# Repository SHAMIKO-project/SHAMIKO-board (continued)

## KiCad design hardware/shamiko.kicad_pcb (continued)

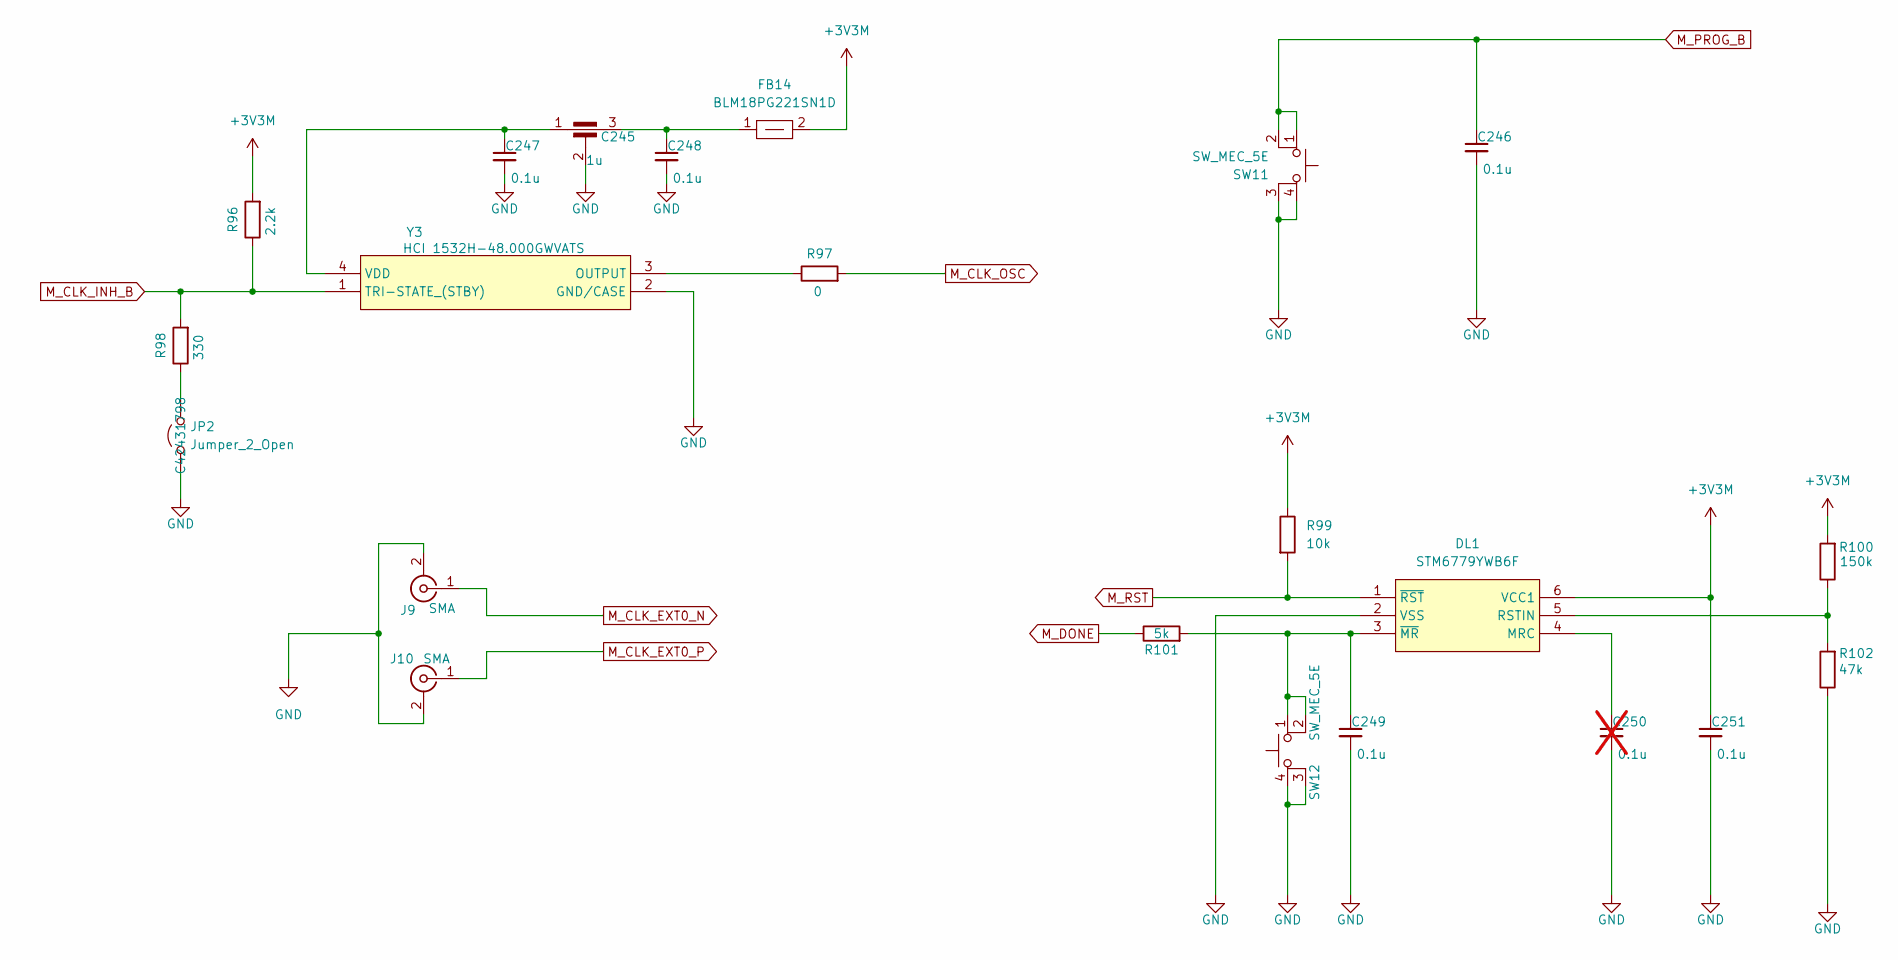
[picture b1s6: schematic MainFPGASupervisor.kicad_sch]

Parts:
C245: 1u; NFM31HK103R1H3L; LCSC C92518
C246, C247, C248, C249, C251: 0.1u; C_0603_1608Metric; LCSC C77055
C250: 0.1u; C_0603_1608Metric; LCSC C77055; not fitted
DL1: STM6779YWB6F; TSOT-23-6; LCSC C2802536
FB14: BLM18PG221SN1D; BLM18SP221SN1B; LCSC C80165
J9, J10: SMA; SMA_Amphenol_132134-14_Vertical; LCSC C3174425
JP2: Jumper_2_Open; PinHeader_1x02_P2.54mm_Vertical; LCSC C42431798
R96: 2.2k; R_0603_1608Metric; LCSC C114662
R97: 0; R_0603_1608Metric; LCSC C100044
R98: 330; R_0603_1608Metric; LCSC C105881
R99: 10k; R_0603_1608Metric; LCSC C95204
R100: 150k; R_0603_1608Metric; LCSC C2906993
R101: 5k; R_0603_1608Metric; LCSC C862232
R102: 47k; R_0603_1608Metric; LCSC C105579
SW11, SW12: SW_MEC_5E; MySW_PUSH_6mm_H5mm; LCSC C393938
Y3: HCI 1532H-48.000GWVATS; 1532H-48_000GWVATS; LCSC C51822787

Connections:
+3V3M: C251.1, DL1.6 (VCC1), FB14.2, R96.2, R99.1, R100.2; also elsewhere on the board
GND: C245.2, C246.2, C247.2, C248.2, C249.2, C250.2, C251.2, DL1.2 (VSS), J9.2 (Ext), J10.2 (Ext), JP2.1 (A), R102.1, SW11.3 (K), SW11.4 (A), SW12.3 (K), SW12.4 (A), Y3.2 (GND/CASE); also elsewhere on the board
M_CLK_EXT0_N: J9.1 (In); also elsewhere on the board
M_CLK_EXT0_P: J10.1 (In); also elsewhere on the board
M_CLK_INH_B: R96.1, R98.2, Y3.1 (TRI-STATE_(STBY)); also elsewhere on the board
M_CLK_OSC: R97.2; also elsewhere on the board
M_DONE: R101.1; also elsewhere on the board
M_PROG_B: C246.1, SW11.1, SW11.2; also elsewhere on the board
M_RST: DL1.1 (~RST), R99.2; also elsewhere on the board
unnamed: C245.3, C248.1, FB14.1
unnamed: C250.1, DL1.4 (MRC)
unnamed: DL1.5 (RSTIN), R100.1, R102.2
unnamed: C249.1, DL1.3 (~MR), R101.2, SW12.1, SW12.2
unnamed: JP2.2 (B), R98.1
unnamed: R97.1, Y3.3 (OUTPUT)
unnamed: C245.1, C247.1, Y3.4 (VDD)

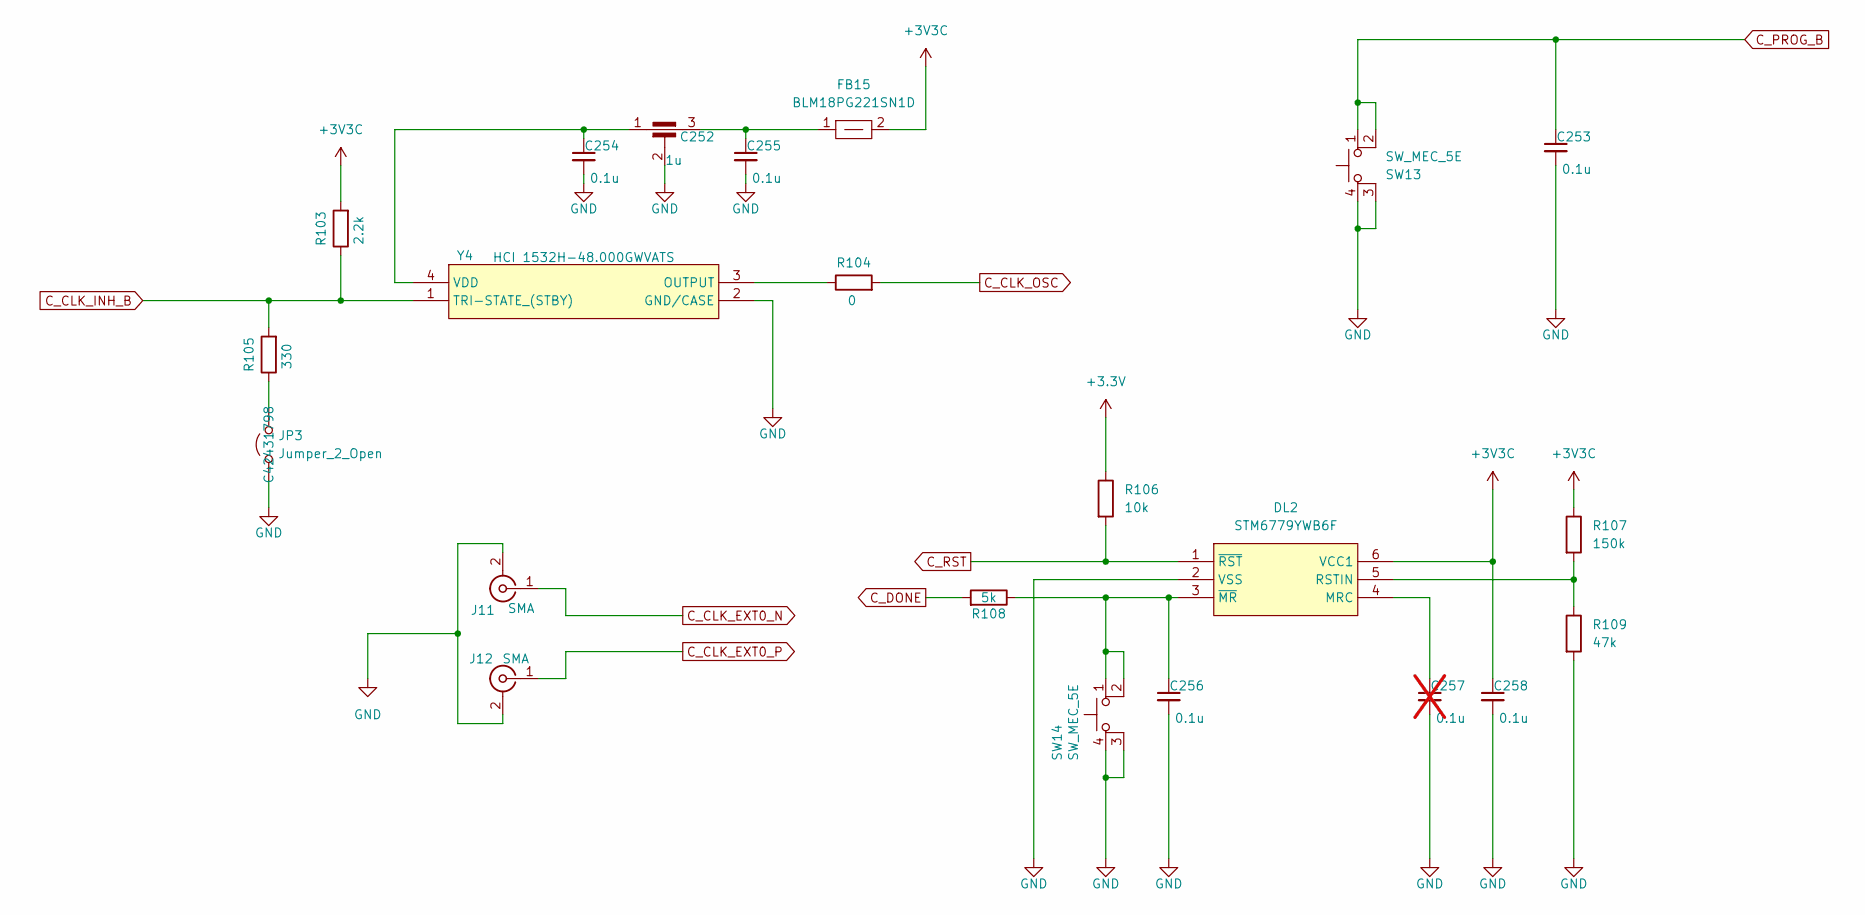
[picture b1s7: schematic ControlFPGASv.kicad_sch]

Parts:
C252: 1u; NFM31HK103R1H3L; LCSC C92518
C253, C254, C255, C256, C258: 0.1u; C_0603_1608Metric; LCSC C77055
C257: 0.1u; C_0603_1608Metric; LCSC C77055; not fitted
DL2: STM6779YWB6F; TSOT-23-6; LCSC C2802536
FB15: BLM18PG221SN1D; BLM18SP221SN1B; LCSC C80165
J11, J12: SMA; SMA_Amphenol_132134-14_Vertical; LCSC C3174425
JP3: Jumper_2_Open; PinHeader_1x02_P2.54mm_Vertical; LCSC C42431798
R103: 2.2k; R_0603_1608Metric; LCSC C114662
R104: 0; R_0603_1608Metric; LCSC C100044
R105: 330; R_0603_1608Metric; LCSC C105881
R106: 10k; R_0603_1608Metric; LCSC C95204
R107: 150k; R_0603_1608Metric; LCSC C2906993
R108: 5k; R_0603_1608Metric; LCSC C862232
R109: 47k; R_0603_1608Metric; LCSC C105579
SW13, SW14: SW_MEC_5E; MySW_PUSH_6mm_H5mm; LCSC C393938
Y4: HCI 1532H-48.000GWVATS; 1532H-48_000GWVATS; LCSC C51822787

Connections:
+3.3V: R106.1; also elsewhere on the board
+3V3C: C258.1, DL2.6 (VCC1), FB15.2, R103.2, R107.1; also elsewhere on the board
C_CLK_EXT0_N: J11.1 (In); also elsewhere on the board
C_CLK_EXT0_P: J12.1 (In); also elsewhere on the board
C_CLK_INH_B: R103.1, R105.2, Y4.1 (TRI-STATE_(STBY)); also elsewhere on the board
C_CLK_OSC: R104.2; also elsewhere on the board
C_DONE: R108.2; also elsewhere on the board
C_PROG_B: C253.1, SW13.1, SW13.2; also elsewhere on the board
C_RST: DL2.1 (~RST), R106.2; also elsewhere on the board
GND: C252.2, C253.2, C254.2, C255.2, C256.2, C257.2, C258.2, DL2.2 (VSS), J11.2 (Ext), J12.2 (Ext), JP3.1 (A), R109.2, SW13.3 (K), SW13.4 (A), SW14.3 (K), SW14.4 (A), Y4.2 (GND/CASE); also elsewhere on the board
unnamed: C252.3, C255.1, FB15.1
unnamed: C257.1, DL2.4 (MRC)
unnamed: DL2.5 (RSTIN), R107.2, R109.1
unnamed: C256.1, DL2.3 (~MR), R108.1, SW14.1, SW14.2
unnamed: JP3.2 (B), R105.1
unnamed: R104.1, Y4.3 (OUTPUT)
unnamed: C252.1, C254.1, Y4.4 (VDD)

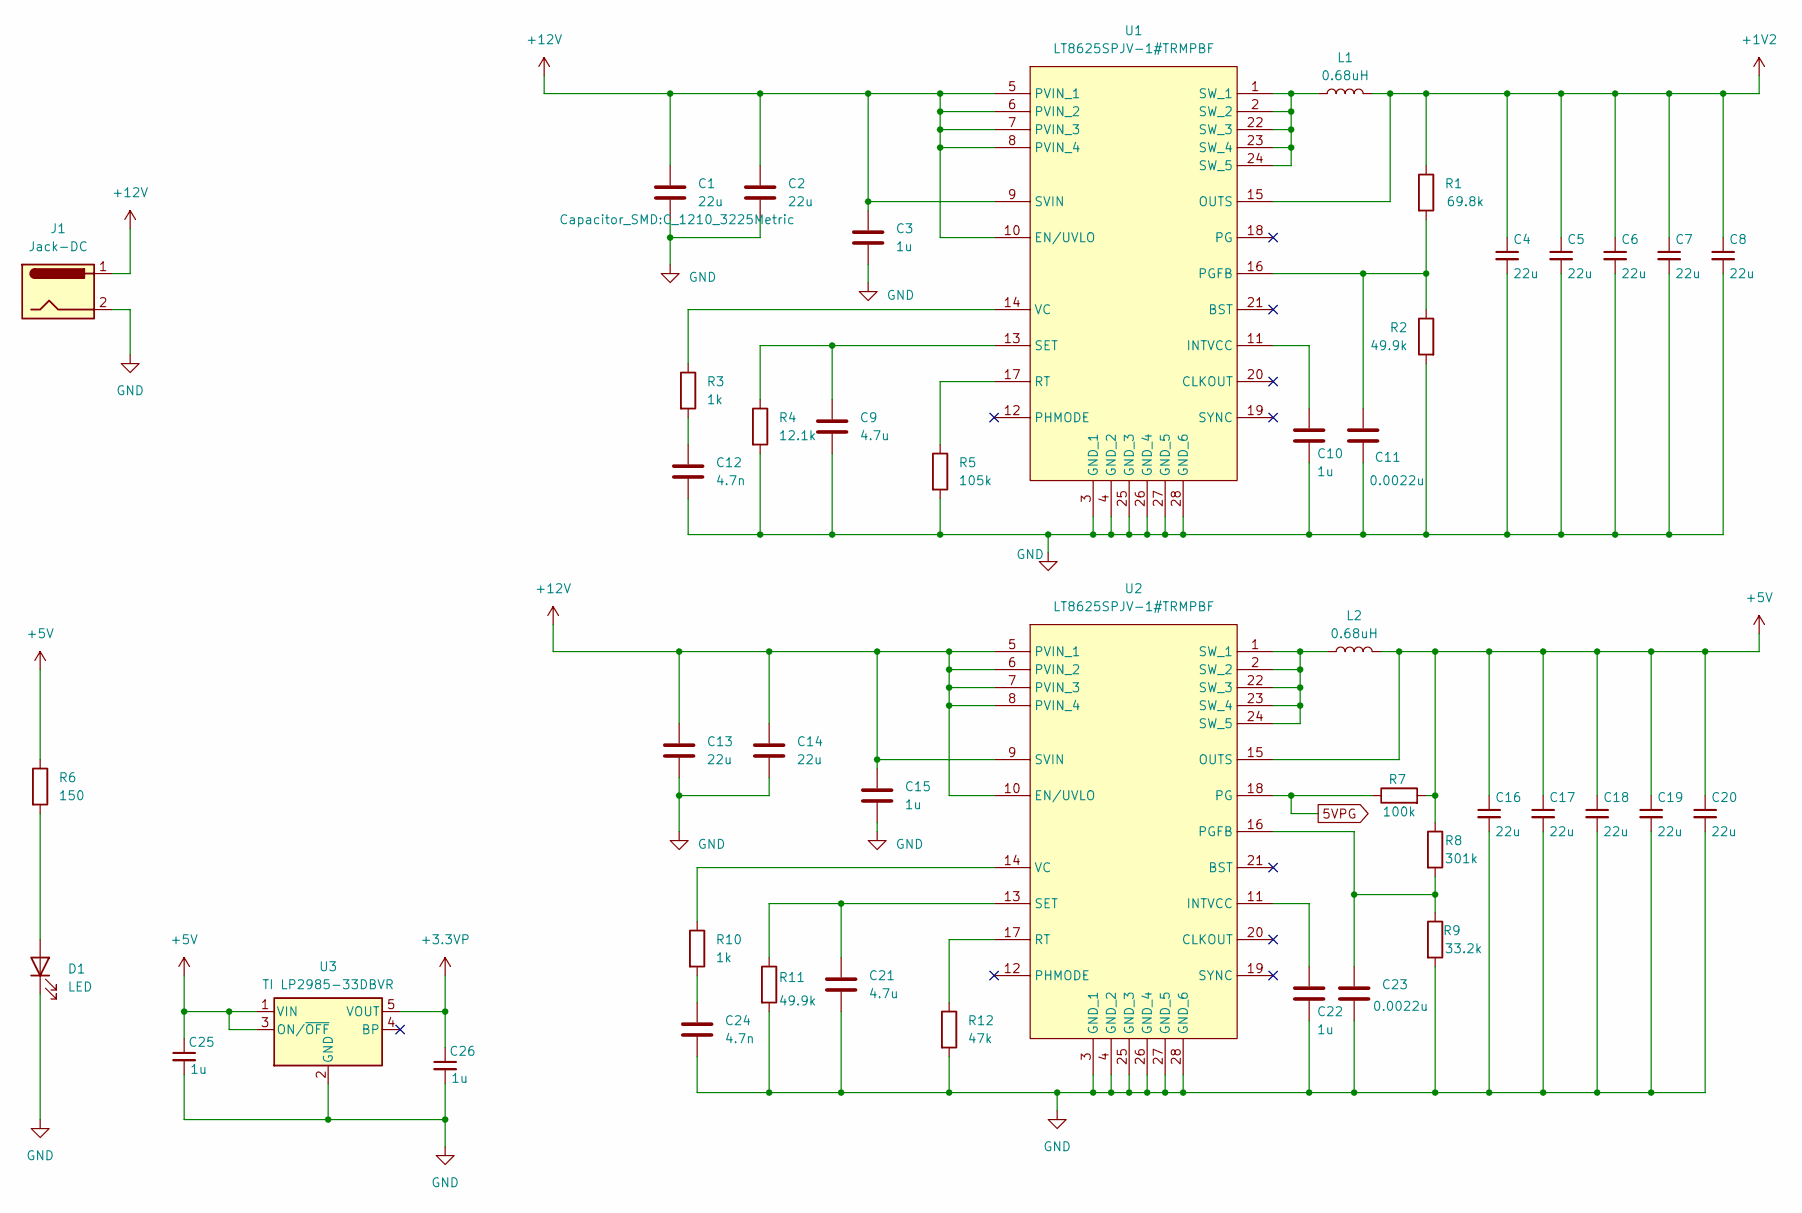
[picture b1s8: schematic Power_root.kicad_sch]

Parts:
C1, C2, C13, C14: 22u; C_1210_3225Metric; LCSC C309062
C3, C15: 1u; C_0805_2012Metric; LCSC C126592
C4, C5, C6, C7, C8, C16, C17, C18, C19, C20: 22u; C_1210_3225Metric; LCSC C21397
C9, C21: 4.7u; C_0603_1608Metric; LCSC C90057
C10, C22, C25, C26: 1u; C_0603_1608Metric; LCSC C77386
C11, C23: 0.0022u; C_0603_1608Metric; LCSC C77033
C12, C24: 4.7n; C_0603_1608Metric; LCSC C85980
D1: LED; LED_0603_1608Metric; LCSC C125103
J1: Jack-DC; CUI_PJ-002A; LCSC C3096082
L1, L2: 0.68uH; XRIM404030SR68MBCA; LCSC C39846865
R1: 69.8k; R_0603_1608Metric; LCSC C861526
R2, R11: 49.9k; R_0603_1608Metric; LCSC C705780
R3, R10: 1k; R_0603_1608Metric; LCSC C22548
R4: 12.1k; R_0603_1608Metric; LCSC C123417
R5: 105k; R_0603_1608Metric; LCSC C861072
R6: 150; R_0603_1608Metric; LCSC C227596
R7: 100k; R_0603_1608Metric; LCSC C25803
R8: 301k; R_0603_1608Metric; LCSC C861309
R9: 33.2k; R_0603_1608Metric; LCSC C2075328
R12: 47k; R_0603_1608Metric; LCSC C105579
U1, U2: LT8625SPJV-1#TRMPBF; LCSC C37130042
U3: TI LP2985-33DBVR; SOT-23-5; LCSC C95414

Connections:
5VPG: R7.1, U2.18 (PG); also elsewhere on the board
+1V2: C4.1, C5.1, C6.1, C7.1, C8.1, L1.2, R1.1, U1.15 (OUTS); also elsewhere on the board
+3.3VP: C26.1, U3.5 (VOUT); also elsewhere on the board
+5V: C16.1, C17.1, C18.1, C19.1, C20.1, C25.1, L2.2, R6.1, R7.2, R8.1, U2.15 (OUTS), U3.1 (VIN), U3.3 (ON/~OFF); also elsewhere on the board
+12V: C1.1, C2.1, C3.1, C13.1, C14.1, C15.1, J1.1, U1.5 (PVIN_1), U1.6 (PVIN_2), U1.7 (PVIN_3), U1.8 (PVIN_4), U1.9 (SVIN), U1.10 (EN/UVLO), U2.5 (PVIN_1), U2.6 (PVIN_2), U2.7 (PVIN_3), U2.8 (PVIN_4), U2.9 (SVIN), U2.10 (EN/UVLO); also elsewhere on the board
GND: C1.2, C2.2, C3.2, C4.2, C5.2, C6.2, C7.2, C8.2, C9.2, C10.2, C11.2, C12.2, C13.2, C14.2, C15.2, C16.2, C17.2, C18.2, C19.2, C20.2, C21.2, C22.2, C23.2, C24.2, C25.2, C26.2, D1.1 (K), J1.2, R2.2, R4.2, R5.2, R9.2, R11.2, R12.2, U1.3 (GND_1), U1.4 (GND_2), U1.25 (GND_3), U1.26 (GND_4), U1.27 (GND_5), U1.28 (GND_6), U2.3 (GND_1), U2.4 (GND_2), U2.25 (GND_3), U2.26 (GND_4), U2.27 (GND_5), U2.28 (GND_6), U3.2 (GND); also elsewhere on the board
unnamed: C12.1, R3.2
unnamed: C24.1, R10.2
unnamed: D1.2 (A), R6.2
unnamed: C10.1, U1.11 (INTVCC)
unnamed: C11.1, R1.2, R2.1, U1.16 (PGFB)
unnamed: R5.1, U1.17 (RT)
unnamed: C9.1, R4.1, U1.13 (SET)
unnamed: L1.1, U1.1 (SW_1), U1.2 (SW_2), U1.22 (SW_3), U1.23 (SW_4), U1.24 (SW_5)
unnamed: R3.1, U1.14 (VC)
unnamed: C22.1, U2.11 (INTVCC)
unnamed: C23.1, R8.2, R9.1, U2.16 (PGFB)
unnamed: R12.1, U2.17 (RT)
unnamed: C21.1, R11.1, U2.13 (SET)
unnamed: L2.1, U2.1 (SW_1), U2.2 (SW_2), U2.22 (SW_3), U2.23 (SW_4), U2.24 (SW_5)
unnamed: R10.1, U2.14 (VC)

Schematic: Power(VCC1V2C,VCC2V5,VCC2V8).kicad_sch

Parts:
C51, C52, C54, C55, C56, C58: 4.7u; C_0603_1608Metric; LCSC C90057
C53, C57, C59: 4.7n; C_0603_1608Metric; LCSC C85980
IC3, IC4, IC5: MCP1727-ADJE_MF; LCSC C635102
R22: 91k; R_0603_1608Metric; LCSC C326721
R23, R27, R28: 100k; R_0603_1608Metric; LCSC C25803
R24: 27k; R_0603_1608Metric; LCSC C309651
R25, R26: 357k; R_0603_1608Metric; LCSC C913223
R29, R30: 51k; R_0603_1608Metric; LCSC C861458
TP3, TP4, TP5: TestPoint; TestPoint_Pad_D1.0mm; LCSC None; not fitted

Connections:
1V8_DELAY: IC3.5 (PWRGD), IC4.3 (~SHDN), IC5.3 (~SHDN), R23.1
5VPG: IC3.3 (~SHDN); also elsewhere on the board
+1V8: C51.1, IC3.8 (VOUT), R22.1, TP3.1; also elsewhere on the board
+3V3C: C55.1, IC5.8 (VOUT), R26.1, R28.2, TP5.1; also elsewhere on the board
+3V3M: C54.1, IC4.8 (VOUT), R25.1, R27.2, TP4.1; also elsewhere on the board
+5V: C52.1, C56.1, C58.1, IC3.1 (VIN_1), IC3.2 (VIN_2), IC4.1 (VIN_1), IC4.2 (VIN_2), IC5.1 (VIN_1), IC5.2 (VIN_2), R23.2; also elsewhere on the board
GND: C51.2, C52.2, C53.2, C54.2, C55.2, C56.2, C57.2, C58.2, C59.2, IC3.4 (GND), IC3.9 (EPAD), IC4.4 (GND), IC4.9 (EPAD), IC5.4 (GND), IC5.9 (EPAD), R24.2, R29.2, R30.2; also elsewhere on the board
unnamed: IC3.7 (ADJ), R22.2, R24.1
unnamed: C53.1, IC3.6 (CDELAY)
unnamed: IC4.7 (ADJ), R25.2, R29.1
unnamed: C57.1, IC4.6 (CDELAY)
unnamed: IC4.5 (PWRGD), R27.1
unnamed: IC5.7 (ADJ), R26.2, R30.1
unnamed: C59.1, IC5.6 (CDELAY)
unnamed: IC5.5 (PWRGD), R28.1

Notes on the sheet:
VCCAUX
Ideal voltage is 1.8V 1.79V = 0.41V*((91000/27000)+1)
Ideal voltage is 3.3V 3.28V = 0.41V*((357000/51000)+1)
VCCIO

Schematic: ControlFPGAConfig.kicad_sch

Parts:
C193, C194, C195: 0.1u; C_0603_1608Metric; LCSC C77055
D5: B_LED; LED_0603_1608Metric; LCSC C19171394
D6, D7: G_LED; LED_0603_1608Metric; LCSC C5342733
J5: JTAG_CONFIG; JTAG_2x7_P2.54mm; LCSC C240854
R48, R49, R50, R57, R58, R59, R61, R62: 4.7k; R_0603_1608Metric; LCSC C99782
R51, R52, R53, R64: 1k; R_0603_1608Metric; LCSC C22548
R54, R55, R56: 200; R_0603_1608Metric; LCSC C2907123
R60: 330; R_0603_1608Metric; LCSC C105881
R63: 2.4k; R_0603_1608Metric; LCSC C22940
SW2: SW_DIP_x03; SW_DIP_SPSTx03_Slide_9.78x9.8mm_W8.61mm_P2.54mm; LCSC C3012353
U5: XC7S25-1CSGA225C; LCSC C1521699
U9: IS25LP064A-JLLE; WSON-8-1EP_8x6mm_P1.27mm_EP3.4x4.3mm; LCSC C1349830
U10, U11: SN74LVC2G17DCKRE4; LCSC C50714

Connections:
+3V3C: C193.1, C194.1, C195.1, D6.2 (A), D7.2 (A), J5.2, R48.1, R49.1, R50.1, R57.1, R58.1, R59.1, R60.1, R61.1, R62.1, R63.1, SW2.1, SW2.2, SW2.3, U9.8 (VCC), U10.5 (VCC), U11.5 (VCC); also elsewhere on the board
/Control FPGA Configuration/CX_JTAG_TCK: U5.E5 (TCK_0), U10.4 (2Y)
/Control FPGA Configuration/CX_JTAG_TDI: U5.L4 (TDI_0), U11.4 (2Y)
/Control FPGA Configuration/CX_JTAG_TDO: R57.2, U5.K4 (TDO_0), U11.1 (1A)
/Control FPGA Configuration/CX_JTAG_TMS: U5.K5 (TMS_0), U10.6 (1Y)
/Control FPGA Configuration/C_CONFIG_M0: R51.1, SW2.6, U5.M5 (M0_0)
/Control FPGA Configuration/C_CONFIG_M1: R52.1, SW2.5, U5.N5 (M1_0)
/Control FPGA Configuration/C_CONFIG_M2: R53.1, SW2.4, U5.M6 (M2_0)
/Control FPGA Configuration/C_JTAG_TCK: J5.6, R49.2, U10.3 (2A)
/Control FPGA Configuration/C_JTAG_TDI: J5.10, R50.2, U11.3 (2A)
/Control FPGA Configuration/C_JTAG_TDO: J5.8, U11.6 (1Y)
/Control FPGA Configuration/C_JTAG_TMS: J5.4, R48.2, U10.1 (1A)
/Control FPGA Configuration/C_S_CLOCK: U5.F5 (CCLK_0), U9.6 (SCK)
/Control FPGA Configuration/C_S_D0: U5.H14 (IO_L1P_T0_D00_MOSI_14), U9.5 (SI_(IO0))
/Control FPGA Configuration/C_S_D1: U5.H15 (IO_L1N_T0_D01_DIN_14), U9.2 (SO_(IO1))
/Control FPGA Configuration/C_S_D2: R62.2, U5.J12 (IO_L2P_T0_D02_14), U9.3 (WP#_(IO2))
/Control FPGA Configuration/C_S_D3: R61.2, U5.K13 (IO_L2N_T0_D03_14), U9.7 (HOLD#_(IO3))
/Control FPGA Configuration/C_S_SELECTn: R63.2, U5.L11 (IO_L6P_T0_FCS_B_14), U9.1 (CE#)
C_DONE: D5.2 (A), R60.2, U5.G5 (DONE_0); also elsewhere on the board
C_INIT_B: R55.2, R59.2, U5.L5 (INIT_B_0)
C_PROG_B: R56.2, R58.2, U5.J5 (PROGRAM_B_0); also elsewhere on the board
GND: C193.2, C194.2, C195.2, J5.1, J5.3, J5.5, J5.7, J5.9, J5.11, J5.13, R51.2, R52.2, R53.2, R54.2, R64.2, U9.4 (GND), U9.9 (EPAD), U10.2 (GND), U11.2 (GND); also elsewhere on the board
unnamed: D5.1 (K), R54.1
unnamed: D6.1 (K), R55.1
unnamed: D7.1 (K), R56.1
unnamed: R64.1, U5.K11 (IO_L3P_T0_DQS_PUDC_B_14)

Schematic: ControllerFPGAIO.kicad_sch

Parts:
U5: XC7S25-1CSGA225C; LCSC C1521699

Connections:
BCBUS0_RXF_B: U5.P2 (IO_L24N_T3_34); also elsewhere on the board
BCBUS1_TXF_B: U5.P3 (IO_L21P_T3_DQS_34); also elsewhere on the board
BCBUS2_RD_B: U5.N2 (IO_L20P_T3_34); also elsewhere on the board
BCBUS3_WR_B: U5.N3 (IO_L21N_T3_DQS_34); also elsewhere on the board
BCBUS4_SIWUA: U5.M4 (IO_L19P_T3_34); also elsewhere on the board
BCBUS5_CLKOUT: U5.M3 (IO_L19N_T3_VREF_34); also elsewhere on the board
BCBUS6_OE_B: U5.K3 (IO_L17P_T2_34); also elsewhere on the board
BCBUS7: U5.J3 (IO_L15N_T2_DQS_34); also elsewhere on the board
BDBUS_D0: U5.N1 (IO_L22N_T3_34); also elsewhere on the board
BDBUS_D1: U5.M1 (IO_L18P_T2_34); also elsewhere on the board
BDBUS_D2: U5.M2 (IO_L20N_T3_34); also elsewhere on the board
BDBUS_D3: U5.L1 (IO_L18N_T2_34); also elsewhere on the board
BDBUS_D4: U5.K1 (IO_L16P_T2_34); also elsewhere on the board
BDBUS_D5: U5.K2 (IO_L17N_T2_34); also elsewhere on the board
BDBUS_D6: U5.J1 (IO_L16N_T2_34); also elsewhere on the board
BDBUS_D7: U5.J2 (IO_L14P_T2_SRCC_34); also elsewhere on the board
C_CLK_EXT0_N: U5.R14 (IO_L12N_T1_MRCC_14); also elsewhere on the board
C_CLK_EXT0_P: U5.R13 (IO_L12P_T1_MRCC_14); also elsewhere on the board
C_CLK_INH_B: U5.R2 (IO_L24P_T3_34); also elsewhere on the board
C_CLK_OSC: U5.M9 (IO_L13P_T2_MRCC_14); also elsewhere on the board
C_DIPSW_0: U5.R8 (IO_L22N_T3_D20_14); also elsewhere on the board
C_DIPSW_1: U5.R7 (IO_L22P_T3_D21_14); also elsewhere on the board
C_DIPSW_2: U5.P7 (IO_L23N_T3_D18_14); also elsewhere on the board
C_DIPSW_3: U5.R6 (IO_L24N_T3_D16_14); also elsewhere on the board
C_DIPSW_4: U5.P6 (IO_L23P_T3_D19_14); also elsewhere on the board
C_DIPSW_5: U5.R5 (IO_L24P_T3_D17_14); also elsewhere on the board
C_DIPSW_6: U5.R4 (IO_L23P_T3_34); also elsewhere on the board
C_DIPSW_7: U5.R3 (IO_L23N_T3_34); also elsewhere on the board
C_HEADER_0: U5.M7 (IO_L19P_T3_D26_14); also elsewhere on the board
C_HEADER_1: U5.M8 (IO_L19N_T3_D25_VREF_14); also elsewhere on the board
C_HEADER_2: U5.N8 (IO_L21P_T3_DQS_14); also elsewhere on the board
C_HEADER_3: U5.N9 (IO_L21N_T3_DQS_D22_14); also elsewhere on the board
C_HEADER_CLK_N: U5.G1 (IO_L12N_T1_MRCC_34); also elsewhere on the board
C_HEADER_CLK_P: U5.H1 (IO_L12P_T1_MRCC_34); also elsewhere on the board
C_LED_0: U5.N7 (IO_L20N_T3_D23_14); also elsewhere on the board
C_LED_1: U5.N6 (IO_L20P_T3_D24_14); also elsewhere on the board
C_LED_2: U5.R12 (IO_L18N_T2_D27_14); also elsewhere on the board
C_LED_3: U5.R11 (IO_L18P_T2_D28_14); also elsewhere on the board
C_LED_4: U5.P11 (IO_L16N_T2_D31_14); also elsewhere on the board
C_LED_5: U5.R10 (IO_L17N_T2_D29_14); also elsewhere on the board
C_LED_6: U5.P10 (IO_L16P_T2_CSI_B_14); also elsewhere on the board
C_LED_7: U5.R9 (IO_L17P_T2_D30_14); also elsewhere on the board
C_RST: U5.J11 (IO_0_14); also elsewhere on the board
C_TACTSW_0: U5.M10 (IO_L13N_T2_MRCC_14); also elsewhere on the board
C_TACTSW_1: U5.P12 (IO_L14N_T2_SRCC_14); also elsewhere on the board
FT600_BE0: U5.H2 (IO_L14N_T2_SRCC_34); also elsewhere on the board
FT600_BE1: U5.H3 (IO_L13N_T2_MRCC_34); also elsewhere on the board
FT600_CLK: U5.F4 (IO_L11P_T1_SRCC_34); also elsewhere on the board
FT600_DATA_0: U5.C4 (IO_L7N_T1_34); also elsewhere on the board
FT600_DATA_1: U5.F3 (IO_L11N_T1_SRCC_34); also elsewhere on the board
FT600_DATA_2: U5.F2 (IO_L10P_T1_34); also elsewhere on the board
FT600_DATA_3: U5.F1 (IO_L10N_T1_34); also elsewhere on the board
FT600_DATA_4: U5.E2 (IO_L8P_T1_34); also elsewhere on the board
FT600_DATA_5: U5.E1 (IO_L8N_T1_34); also elsewhere on the board
FT600_DATA_6: U5.D2 (IO_L6P_T0_34); also elsewhere on the board
FT600_DATA_7: U5.D1 (IO_L6N_T0_VREF_34); also elsewhere on the board
FT600_DATA_8: U5.C1 (IO_L4P_T0_34); also elsewhere on the board
FT600_DATA_9: U5.B1 (IO_L4N_T0_34); also elsewhere on the board
FT600_DATA_10: U5.B2 (IO_L2P_T0_34); also elsewhere on the board
FT600_DATA_11: U5.A2 (IO_L2N_T0_34); also elsewhere on the board
FT600_DATA_12: U5.B3 (IO_L3N_T0_DQS_34); also elsewhere on the board
FT600_DATA_13: U5.A3 (IO_L1N_T0_34); also elsewhere on the board
FT600_DATA_14: U5.B4 (IO_L3P_T0_DQS_34); also elsewhere on the board
FT600_DATA_15: U5.A4 (IO_L1P_T0_34); also elsewhere on the board
FT600_GPIO0: U5.C5 (IO_L5P_T0_34); also elsewhere on the board
FT600_GPIO1: U5.B5 (IO_L5N_T0_34); also elsewhere on the board
FT600_OE: U5.D3 (IO_L9N_T1_DQS_34); also elsewhere on the board
FT600_RD: U5.E3 (IO_L9P_T1_DQS_34); also elsewhere on the board
FT600_RXF: U5.L10 (IO_25_14); also elsewhere on the board
FT600_SIWU: U5.G4 (IO_0_34); also elsewhere on the board
FT600_TXE: U5.H4 (IO_L13P_T2_MRCC_34); also elsewhere on the board
FT600_WAKEUP: U5.D4 (IO_L7P_T1_34); also elsewhere on the board
FT600_WR: U5.N4 (IO_25_34); also elsewhere on the board
MC_IC_CTRL0: U5.C13 (IO_L15P_T2_DQS_15); also elsewhere on the board
MC_IC_CTRL1: U5.E11 (IO_L17N_T2_15); also elsewhere on the board
MC_IC_CTRL2: U5.F11 (IO_L17P_T2_15); also elsewhere on the board
MC_IC_CTRL3: U5.G11 (IO_L23P_T3_15); also elsewhere on the board
MC_IC_CTRL4: U5.H11 (IO_25_15); also elsewhere on the board
MC_IC_D0: U5.A5 (IO_L5P_T0_AD2P_15); also elsewhere on the board
MC_IC_D1: U5.A6 (IO_L5N_T0_AD2N_15); also elsewhere on the board
MC_IC_D2: U5.B6 (IO_L3P_T0_DQS_AD1P_15); also elsewhere on the board
MC_IC_D3: U5.A7 (IO_L3N_T0_DQS_AD1N_15); also elsewhere on the board
MC_IC_D4: U5.A8 (IO_L6P_T0_15); also elsewhere on the board
MC_IC_D5: U5.A9 (IO_L6N_T0_VREF_15); also elsewhere on the board
MC_IC_D6: U5.B9 (IO_L9P_T1_DQS_AD11P_15); also elsewhere on the board
MC_IC_D7: U5.A10 (IO_L9N_T1_DQS_AD11N_15); also elsewhere on the board
MC_IC_D8: U5.B10 (IO_L8N_T1_AD3N_15); also elsewhere on the board
MC_IC_D9: U5.A11 (IO_L11P_T1_SRCC_AD12P_15); also elsewhere on the board
MC_IC_D10: U5.B11 (IO_L10P_T1_AD4P_15); also elsewhere on the board
MC_IC_D11: U5.A12 (IO_L11N_T1_SRCC_AD12N_15); also elsewhere on the board
MC_IC_D12: U5.B12 (IO_L10N_T1_AD4N_15); also elsewhere on the board
MC_IC_D13: U5.A13 (IO_L12P_T1_MRCC_AD5P_15); also elsewhere on the board
MC_IC_D14: U5.B13 (IO_L13P_T2_MRCC_15); also elsewhere on the board
MC_IC_D15: U5.A14 (IO_L12N_T1_MRCC_AD5N_15); also elsewhere on the board
MC_IC_D16: U5.B14 (IO_L13N_T2_MRCC_15); also elsewhere on the board
MC_IC_D17: U5.B15 (IO_L14N_T2_SRCC_15); also elsewhere on the board
MC_IC_D18: U5.C14 (IO_L15N_T2_DQS_15); also elsewhere on the board
MC_IC_D19: U5.C15 (IO_L14P_T2_SRCC_15); also elsewhere on the board
MC_IC_D20: U5.D15 (IO_L19N_T3_VREF_15); also elsewhere on the board
MC_IC_D21: U5.E14 (IO_L19P_T3_15); also elsewhere on the board
MC_IC_D22: U5.E15 (IO_L21N_T3_DQS_15); also elsewhere on the board
MC_IC_D23: U5.F14 (IO_L21P_T3_DQS_15); also elsewhere on the board
MC_IC_D24: U5.F15 (IO_L20N_T3_15); also elsewhere on the board
MC_IC_D25: U5.G14 (IO_L22N_T3_15); also elsewhere on the board
MC_IC_D26: U5.G15 (IO_L20P_T3_15); also elsewhere on the board
MC_IC_D27: U5.J15 (IO_L5P_T0_D06_14); also elsewhere on the board
MC_IC_D28: U5.K14 (IO_L4P_T0_D04_14); also elsewhere on the board
MC_IC_D29: U5.K15 (IO_L5N_T0_D07_14); also elsewhere on the board
MC_IC_D30: U5.L14 (IO_L7N_T1_D10_14); also elsewhere on the board
MC_IC_D31: U5.L15 (IO_L4N_T0_D05_14); also elsewhere on the board
MC_IC_D32: U5.M14 (IO_L9P_T1_DQS_14); also elsewhere on the board
MC_IC_D33: U5.M15 (IO_L9N_T1_DQS_D13_14); also elsewhere on the board
MC_IC_D34: U5.N14 (IO_L10P_T1_D14_14); also elsewhere on the board
MC_IC_D35: U5.N15 (IO_L10N_T1_D15_14); also elsewhere on the board
MC_IC_D36: U5.P15 (IO_L11N_T1_SRCC_14); also elsewhere on the board
MC_IC_D37: U5.P14 (IO_L11P_T1_SRCC_14); also elsewhere on the board
MC_IC_D38: U5.C6 (IO_L1P_T0_AD0P_15); also elsewhere on the board
MC_IC_D39: U5.D7 (IO_L2P_T0_AD8P_15); also elsewhere on the board
MC_IC_D40: U5.C7 (IO_L1N_T0_AD0N_15); also elsewhere on the board
MC_IC_D41: U5.D8 (IO_L2N_T0_AD8N_15); also elsewhere on the board
MC_IC_D42: U5.C8 (IO_L4P_T0_AD9P_15); also elsewhere on the board
MC_IC_D43: U5.D9 (IO_L7P_T1_AD10P_15); also elsewhere on the board
MC_IC_D44: U5.C9 (IO_L4N_T0_AD9N_15); also elsewhere on the board
MC_IC_D45: U5.D10 (IO_L7N_T1_AD10N_15); also elsewhere on the board
MC_IC_D46: U5.C10 (IO_L8P_T1_AD3P_15); also elsewhere on the board
MC_IC_D47: U5.D11 (IO_0_15); also elsewhere on the board
MC_IC_D48: U5.D12 (IO_L16P_T2_15); also elsewhere on the board
MC_IC_D49: U5.D13 (IO_L16N_T2_15); also elsewhere on the board
MC_IC_D50: U5.E12 (IO_L18P_T2_15); also elsewhere on the board
MC_IC_D51: U5.E13 (IO_L18N_T2_15); also elsewhere on the board
MC_IC_D52: U5.G12 (IO_L23N_T3_15); also elsewhere on the board
MC_IC_D53: U5.G13 (IO_L22P_T3_15); also elsewhere on the board
MC_IC_D54: U5.H12 (IO_L24P_T3_RS1_15); also elsewhere on the board
MC_IC_D55: U5.H13 (IO_L24N_T3_RS0_15); also elsewhere on the board
MC_IC_D56: U5.K12 (IO_L3N_T0_DQS_EMCCLK_14); also elsewhere on the board
MC_IC_D57: U5.L12 (IO_L6N_T0_D08_VREF_14); also elsewhere on the board
MC_IC_D58: U5.L13 (IO_L7P_T1_D09_14); also elsewhere on the board
MC_IC_D59: U5.M13 (IO_L8P_T1_D11_14); also elsewhere on the board
MC_IC_D60: U5.N12 (IO_L14P_T2_SRCC_14); also elsewhere on the board
MC_IC_D61: U5.N13 (IO_L8N_T1_D12_14); also elsewhere on the board
MC_IC_D62: U5.N11 (IO_L15N_T2_DQS_DOUT_CSO_B_14); also elsewhere on the board
MC_IC_D63: U5.N10 (IO_L15P_T2_DQS_RDWR_B_14); also elsewhere on the board
PWREN_B: U5.J4 (IO_L15P_T2_DQS_34); also elsewhere on the board
SUSPEND_B: U5.P1 (IO_L22P_T3_34); also elsewhere on the board

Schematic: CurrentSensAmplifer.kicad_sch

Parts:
C259: 1u; C_0805_2012Metric; LCSC C126592
C260: 0.01u; C_0603_1608Metric; LCSC C85973
C261: 10u; C_0805_2012Metric; LCSC C126586
C262: 1u; C_0603_1608Metric; LCSC C77386
C263, C267, C268, C272: 0.1u; C_0603_1608Metric; LCSC C77055
C264, C269, C270, C271: 10u; C_0805_2012Metric; LCSC C440198
C265, C266, C273: 1n; C_0603_1608Metric; LCSC C77026
FB16: BLM18PG221SN1D; BLM18SP221SN1B; LCSC C80165
IC8: LT1763CS8-5#PBF; SSOP-8_3.95x5.21x3.27mm_P1.27mm; LCSC C117275
J13: SMA; SMA_Amphenol_132134-14_Vertical; LCSC C3174425
R110, R111: 402; R_0603_1608Metric; LCSC C666875
R112: 0; R_0603_1608Metric; LCSC C100044
R113: 49.9; R_0603_1608Metric; LCSC C861434
R114: 357; R_0603_1608Metric; LCSC C23028
R115: 806; R_0603_1608Metric; LCSC C2692785
R116: 40.2; R_0603_1608Metric; LCSC C2999484
R117: 62; R_1210_3225Metric; LCSC C230313
U19: AD8000; AD8000YRDZ; LCSC C652140

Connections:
+1V0M: R112.2; also elsewhere on the board
+12V: FB16.2; also elsewhere on the board
GND: C259.2, C261.2, C262.2, C263.2, C264.2, C271.2, C272.2, C273.2, IC8.3 (GND_1), IC8.6 (GND_2), IC8.7 (GND_3), J13.2 (Ext), R115.1, R117.1, U19.4 (-VS), U19.9 (EP); also elsewhere on the board
unnamed: C264.1, R110.1, R111.2
unnamed: C265.1, C267.1, C269.1, R112.1, R117.2
unnamed: C266.2, C268.2, C270.2, R113.1
unnamed: C271.1, C272.1, C273.1, R116.1
unnamed: C260.2, IC8.4 (BYP)
unnamed: C259.1, FB16.1, IC8.5 (~SHDN), IC8.8 (IN)
unnamed: J13.1 (In), R113.2
unnamed: C265.2, C267.2, C269.2, R111.1, R115.2, U19.3 (+IN)
unnamed: R114.1, R116.2, U19.2 (-IN)
unnamed: R114.2, U19.1 (FEEDBACK)
unnamed: C266.1, C268.1, C270.1, U19.6 (OUTPUT)
VDDA: C260.1, C261.1, C262.1, C263.1, IC8.1 (OUT), IC8.2 (SENSE/ADJ), R110.2, U19.7 (+VS), U19.8 (~POWER_DOWN)

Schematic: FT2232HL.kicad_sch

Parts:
C202, C204, C205, C206, C207, C209, C210, C211, C212, C214, C216, C217, C219, C222: 0.1u; C_0603_1608Metric; LCSC C77055
C203: 47u; C_0805_2012Metric; LCSC C76636
C208, C213, C215: 1u; NFM31HK103R1H3L; LCSC C92518
C218: 3.3u; C_0603_1608Metric; LCSC C5360803
C220, C221: 27p; C_0603_1608Metric; LCSC C107045
FB5, FB6, FB7, FB8: BLM18PG221SN1D; BLM18SP221SN1B; LCSC C80165
FL1: DLW21HN900SQ2L; LCSC C80529
IC6: FT2232HL-TRAY; LQFP-64_10x10mm_P0.5mm; LCSC C27882
IC7: AT93C46DN-SH-B; SSOP-8_3.9x5.05mm_P1.27mm; LCSC C6499
P1: USB_C_Plug_USB2.0; USB_C_Receptacle_G-Switch_GT-USB-7010ASV; LCSC C2988369
R83, R87, R88, R89, R92: 10k; R_0603_1608Metric; LCSC C95204
R84, R85: 5.1k; R_0603_1608Metric; LCSC C23186
R86: 12k; R_0603_1608Metric; LCSC C705807
R90: 2.2k; R_0603_1608Metric; LCSC C114662
R91: 4.7k; R_0603_1608Metric; LCSC C99782
RN6, RN7, RN8, RN9, RN10, RN11, RN12, RN13: 2.2k; YAGEO_R_network; LCSC C136829
U12: LM2937IMP-3.3; SOT-223; LCSC C140265
U13: TPD2EUSB30; Texas_DRT-3; LCSC C97502
Y1: 12MHz; Crystal_SMD_5032-2Pin_5.0x3.2mm; LCSC C112573

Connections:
+3.3V: C203.1, C208.3, C217.1, C219.1, FB5.1, FB6.1, IC6.50 (VREGIN), IC7.6 (ORG), IC7.8 (VCC), R87.1, R88.1, R89.1, RN6.1, RN6.2, RN6.3, RN6.4, RN7.1, RN7.2, RN7.3, RN7.4, RN8.1, RN8.2, RN8.3, RN8.4, RN9.1, RN9.2, RN9.3, RN9.4, RN10.1, RN10.2, RN10.3, RN10.4, RN11.1, RN11.2, RN11.3, RN11.4, RN12.1, RN12.2, RN12.3, RN12.4, RN13.1, RN13.2, RN13.3, RN13.4, U12.3 (VO); also elsewhere on the board
+5V: C202.1, U12.1 (VI); also elsewhere on the board
/FT2232HL/D+: FL1.1, P1.A6 (D+), U13.1 (D+)
/FT2232HL/D-: FL1.4, P1.A7 (D-), U13.2 (D-)
/FT2232HL/FT232_D+: FL1.2, IC6.8 (DP)
/FT2232HL/FT232_D-: FL1.3, IC6.7 (DM)
ACBUS0_RXF_B: IC6.26 (ACBUS0), RN6.8; also elsewhere on the board
ACBUS1_TXF_B: IC6.27 (ACBUS1), RN6.7; also elsewhere on the board
ACBUS2_RD_B: IC6.28 (ACBUS2), RN6.6; also elsewhere on the board
ACBUS3_WR_B: IC6.29 (ACBUS3), RN6.5; also elsewhere on the board
ACBUS4_SIWUA: IC6.30 (ACBUS4), RN7.8; also elsewhere on the board
ACBUS5_CLKOUT: IC6.32 (ACBUS5), RN7.7; also elsewhere on the board
ACBUS6_OE_B: IC6.33 (ACBUS6), RN7.6; also elsewhere on the board
ACBUS7: IC6.34 (ACBUS7), RN7.5; also elsewhere on the board
ADBUS_D0: IC6.16 (ADBUS0), RN8.8; also elsewhere on the board
ADBUS_D1: IC6.17 (ADBUS1), RN8.7; also elsewhere on the board
ADBUS_D2: IC6.18 (ADBUS2), RN8.6; also elsewhere on the board
ADBUS_D3: IC6.19 (ADBUS3), RN8.5; also elsewhere on the board
ADBUS_D4: IC6.21 (ADBUS4), RN9.8; also elsewhere on the board
ADBUS_D5: IC6.22 (ADBUS5), RN9.7; also elsewhere on the board
ADBUS_D6: IC6.23 (ADBUS6), RN9.6; also elsewhere on the board
ADBUS_D7: IC6.24 (ADBUS7), RN9.5; also elsewhere on the board
BCBUS0_RXF_B: IC6.48 (BCBUS0), RN13.8; also elsewhere on the board
BCBUS1_TXF_B: IC6.52 (BCBUS1), RN13.7; also elsewhere on the board
BCBUS2_RD_B: IC6.53 (BCBUS2), RN13.6; also elsewhere on the board
BCBUS3_WR_B: IC6.54 (BCBUS3), RN13.5; also elsewhere on the board
BCBUS4_SIWUA: IC6.55 (BCBUS4), RN12.8; also elsewhere on the board
BCBUS5_CLKOUT: IC6.57 (BCBUS5), RN12.7; also elsewhere on the board
BCBUS6_OE_B: IC6.58 (BCBUS6), RN12.6; also elsewhere on the board
BCBUS7: IC6.59 (BCBUS7), R91.2, R92.1; also elsewhere on the board
BDBUS_D0: IC6.38 (BDBUS0), RN11.8; also elsewhere on the board
BDBUS_D1: IC6.39 (BDBUS1), RN11.7; also elsewhere on the board
BDBUS_D2: IC6.40 (BDBUS2), RN11.6; also elsewhere on the board
BDBUS_D3: IC6.41 (BDBUS3), RN11.5; also elsewhere on the board
BDBUS_D4: IC6.43 (BDBUS4), RN10.8; also elsewhere on the board
BDBUS_D5: IC6.44 (BDBUS5), RN10.7; also elsewhere on the board
BDBUS_D6: IC6.45 (BDBUS6), RN10.6; also elsewhere on the board
BDBUS_D7: IC6.46 (BDBUS7), RN10.5; also elsewhere on the board
C_RST: IC6.14 (RESET#); also elsewhere on the board
GND: C202.2, C203.2, C204.2, C205.2, C206.2, C207.2, C208.2, C209.2, C210.2, C211.2, C212.2, C213.2, C214.2, C215.2, C216.2, C217.2, C218.2, C219.2, C220.1, C221.1, C222.2, FB7.2, FB8.2, IC6.1 (GND_1), IC6.5 (GND_2), IC6.10 (AGND), IC6.11 (GND_3), IC6.13 (TEST), IC6.15 (GND_4), IC6.25 (GND_5), IC6.35 (GND_6), IC6.47 (GND_7), IC6.51 (GND_8), IC7.5 (GND), R83.2, R84.2, R85.2, R86.1, R92.2, U12.2 (GND), U12.4 (GND), U13.3 (GND); also elsewhere on the board
unnamed: C213.1, C214.1, FB5.2
unnamed: C215.1, C216.1, FB6.2
unnamed: FB7.1, P1.A1 (GND), P1.A12 (GND), P1.B1 (GND), P1.B12 (GND)
unnamed: IC6.62 (EECLK), IC7.2 (SK), R88.2
unnamed: IC6.63 (EECS), IC7.1 (CS), R89.2
unnamed: IC6.61 (EEDATA), IC7.3 (DI), R90.2
unnamed: C220.2, IC6.2 (OSCI), Y1.2
unnamed: C221.2, IC6.3 (OSCO), Y1.1
unnamed: IC6.6 (REF), R86.2
unnamed: C208.1, C209.1, C210.1, C211.1, C212.1, IC6.20 (VCCIO_1), IC6.31 (VCCIO_2), IC6.42 (VCCIO_3), IC6.56 (VCCIO_4)
unnamed: C204.1, C205.1, C206.1, C207.1, C218.1, IC6.12 (VCORE_1), IC6.37 (VCORE_2), IC6.49 (VREGOUT), IC6.64 (VCORE_3)
unnamed: C215.3, IC6.4 (VPHY)
unnamed: C213.3, IC6.9 (VPLL)
unnamed: IC7.4 (DO), R87.2, R90.1
unnamed: P1.A5 (CC), R84.1
unnamed: FB8.1, P1.S1 (SHIELD)
unnamed: P1.B5 (VCONN), R85.1
PWREN_B: IC6.60 (PWREN#); also elsewhere on the board
SUSPEND_B: IC6.36 (SUSPEND#); also elsewhere on the board
VBUS_FT323H: C222.1, P1.A4 (VBUS), P1.A9 (VBUS), P1.B4 (VBUS), P1.B9 (VBUS), R83.1, R91.1
